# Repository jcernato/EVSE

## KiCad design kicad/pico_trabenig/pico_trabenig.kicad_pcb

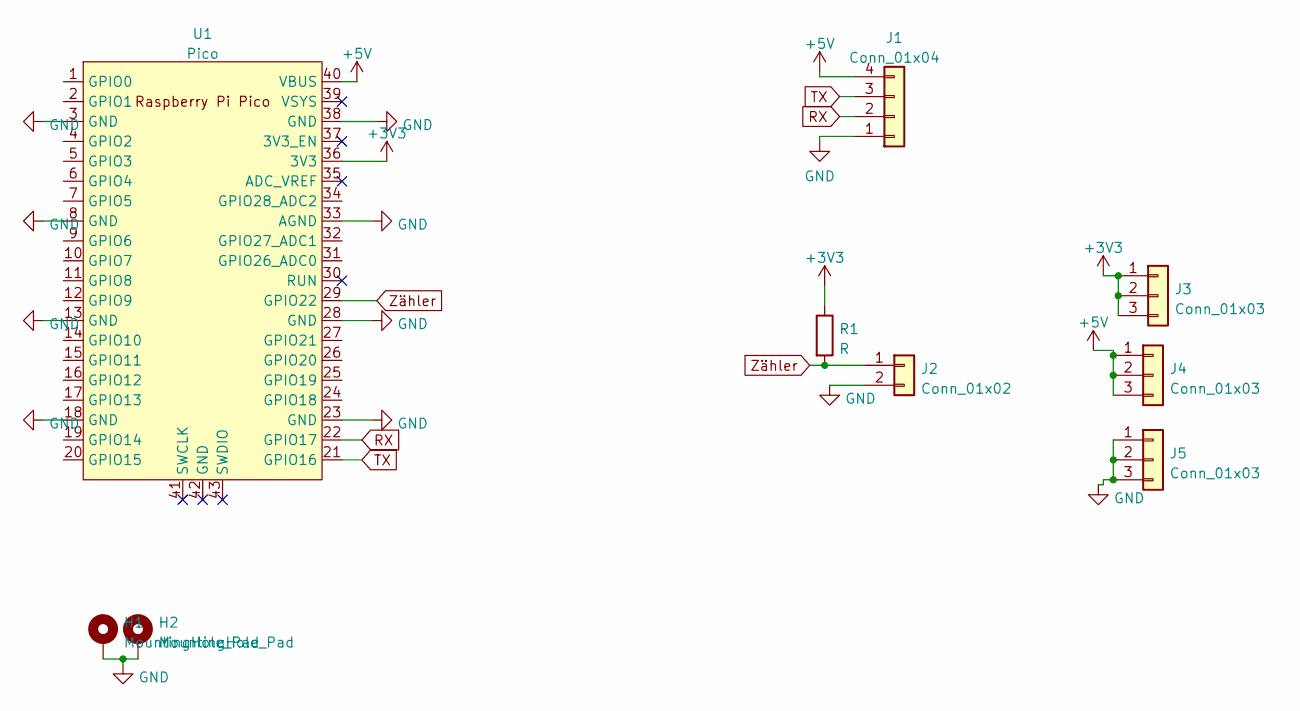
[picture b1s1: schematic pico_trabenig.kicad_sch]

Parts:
H1, H2: MountingHole_Pad; MountingHole_3.2mm_M3_DIN965_Pad
J1: Conn_01x04; JST_XH_B4B-XH-A_1x04_P2.50mm_Vertical
J2: Conn_01x02; JST_XH_B2B-XH-A_1x02_P2.50mm_Vertical
J3, J4, J5: Conn_01x03; PinSocket_1x03_P2.54mm_Vertical
R1: R; R_1206_3216Metric
U1: Pico; RPi_Pico_SMD_TH

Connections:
+3V3: J3.1, J3.2, J3.3, R1.1, U1.36 (3V3)
+5V: J1.4, J4.1, J4.2, J4.3, U1.40 (VBUS)
GND: H1.1, H2.1, J1.1, J2.2, J5.1, J5.2, J5.3, U1.3 (GND), U1.8 (GND), U1.13 (GND), U1.18 (GND), U1.23 (GND), U1.28 (GND), U1.33 (AGND), U1.38 (GND)
RX: J1.2, U1.22 (GPIO17)
TX: J1.3, U1.21 (GPIO16)
Zähler: J2.1, R1.2, U1.29 (GPIO22)

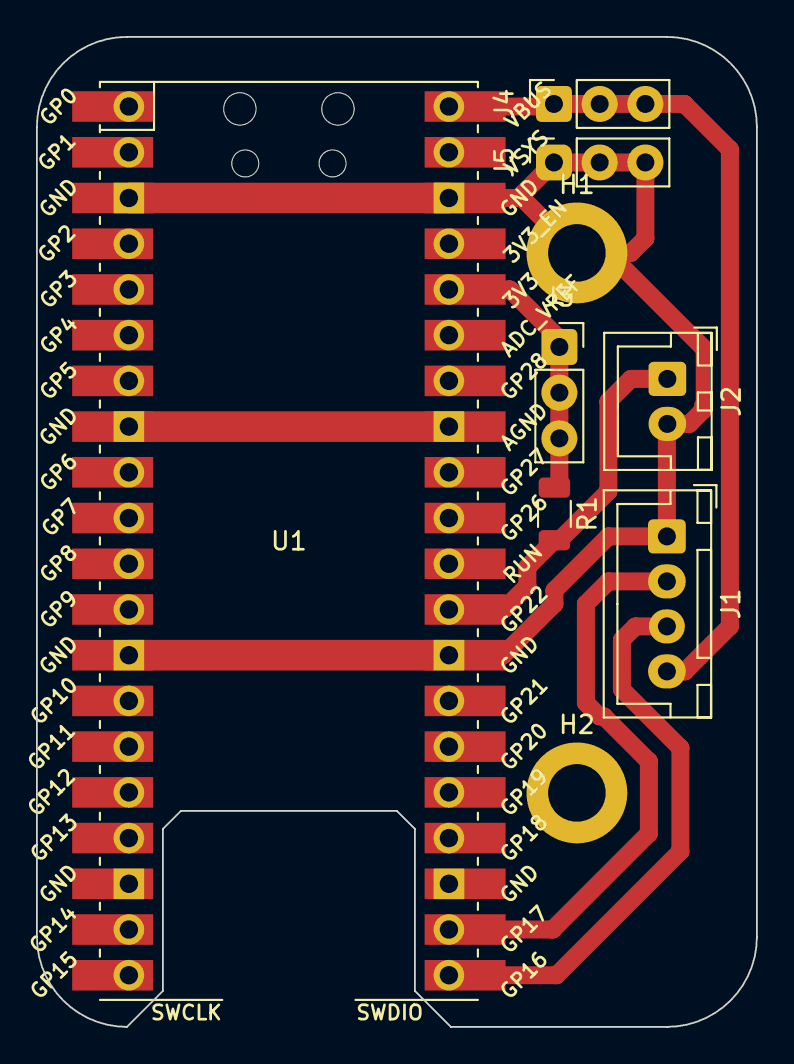
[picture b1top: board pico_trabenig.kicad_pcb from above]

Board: 2 copper layers, 40.0 x 55.0 mm, 9 parts (0 on the bottom side), 6 nets.

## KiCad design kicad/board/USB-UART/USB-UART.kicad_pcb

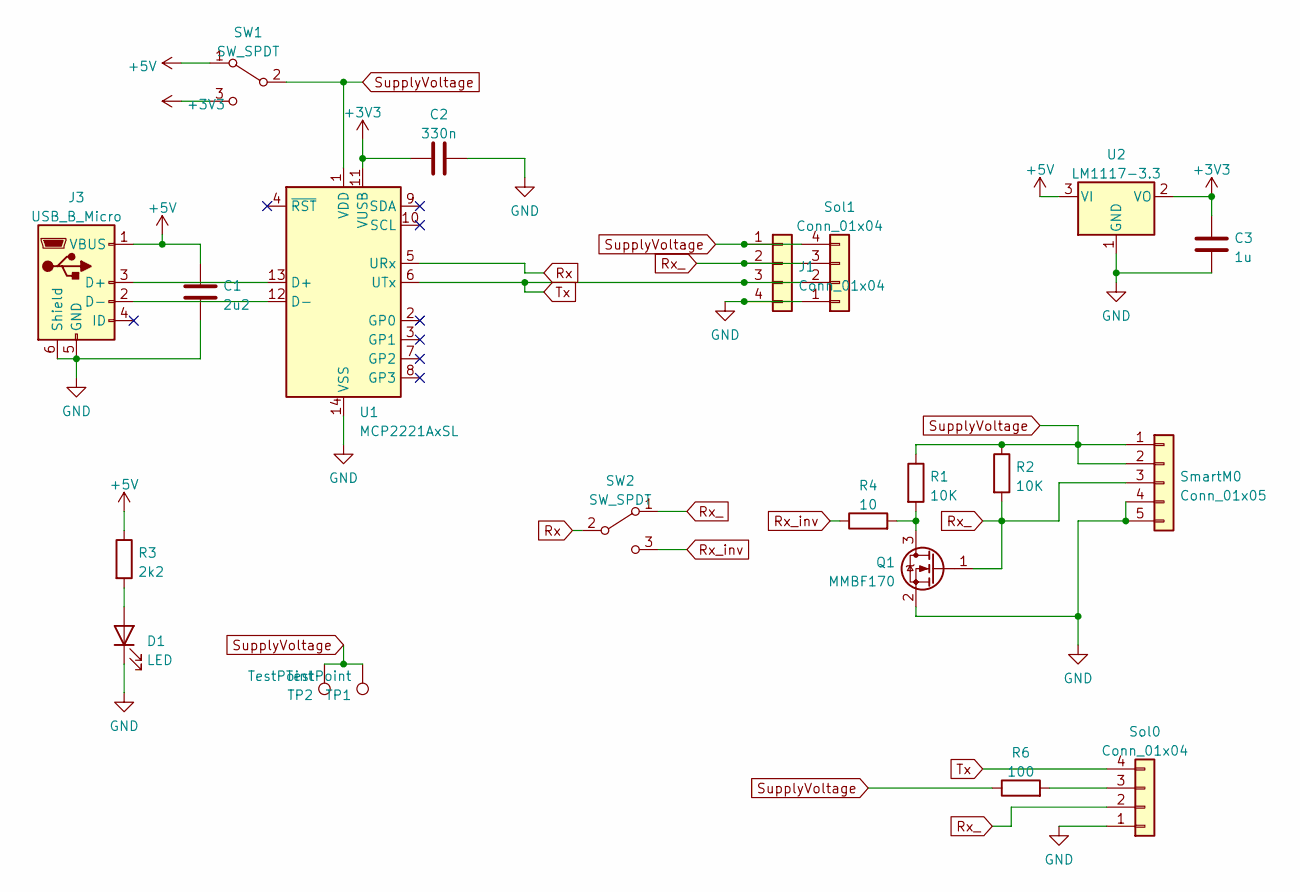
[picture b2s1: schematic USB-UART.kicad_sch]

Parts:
C1: 2u2; C_Radial_D5.0mm_H5.0mm_P2.00mm
C2: 330n; C_1206_3216Metric
C3: 1u; C_1206_3216Metric
D1: LED; LED_1206_3216Metric
J1: Conn_01x04; Molex_KK-254_AE-6410-04A_1x04_P2.54mm_Vertical
J3: USB_B_Micro; USB_Mini-B_Wuerth_65100516121_Horizontal
Q1: MMBF170; SOT-23
R1, R2: 10K; R_1206_3216Metric
R3: 2k2; R_1206_3216Metric
R4: 10; R_1206_3216Metric
R6: 100; R_1206_3216Metric
SW1, SW2: SW_SPDT; SW_Slide_1P2T_CK_OS102011MS2Q
SmartM0: Conn_01x05; JST_PH_B5B-PH-K_1x05_P2.00mm_Vertical
Sol0, Sol1: Conn_01x04; JST_PH_B4B-PH-K_1x04_P2.00mm_Vertical
TP1, TP2: TestPoint; Pin_D1.0mm_L10.0mm
U1: MCP2221AxSL; SOIC-14_3.9x8.7mm_P1.27mm
U2: LM1117-3.3; SOT-223-3_TabPin2

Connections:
+3V3: C2.1, C3.2, SW1.3 (C), U1.11 (VUSB), U2.2 (VO)
+5V: C1.2, J3.1 (VBUS), R3.1, SW1.1 (A), U2.3 (VI)
GND: C1.1, C2.2, C3.1, D1.1 (K), J1.4, J3.5 (GND), J3.6 (Shield), Q1.2 (S), SmartM0.4, SmartM0.5, Sol0.1, Sol1.1, U1.14 (VSS), U2.1 (GND)
unnamed: D1.2 (A), R3.2
unnamed: J3.2 (D-), U1.12 (D-)
unnamed: J3.3 (D+), U1.13 (D+)
unnamed: Q1.3 (D), R1.2, R4.2
unnamed: R6.2, Sol0.3
Rx: SW2.2 (B), U1.5 (URx)
Rx_: J1.2, Q1.1 (G), R2.2, SW2.1 (A), SmartM0.3, Sol0.2, Sol1.3
Rx_inv: R4.1, SW2.3 (C)
SupplyVoltage: J1.1, R1.1, R2.1, R6.1, SW1.2 (B), SmartM0.1, SmartM0.2, Sol1.4, TP1.1, TP2.1, U1.1 (VDD)
Tx: J1.3, Sol0.4, Sol1.2, U1.6 (UTx)

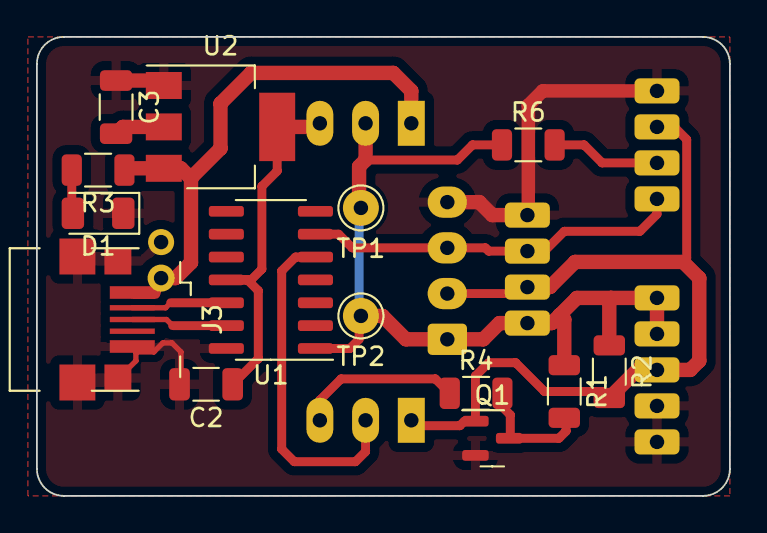
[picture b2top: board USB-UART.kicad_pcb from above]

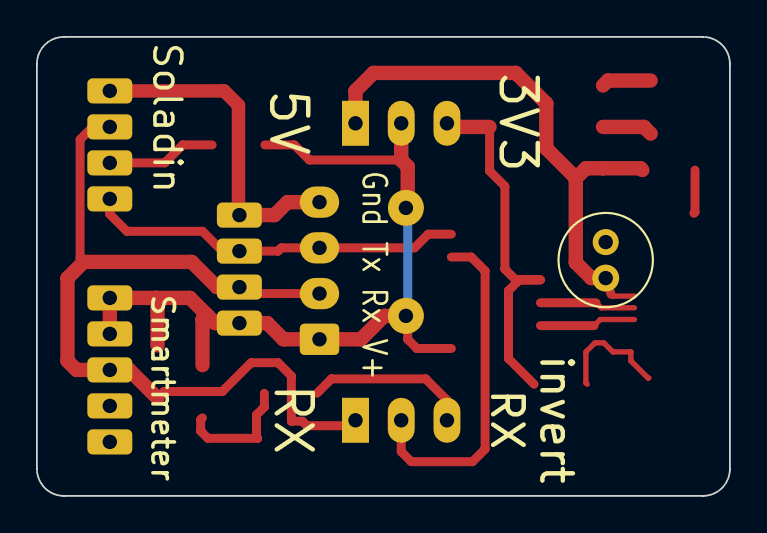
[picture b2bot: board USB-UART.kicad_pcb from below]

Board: 2 copper layers, 38.5 x 25.5 mm, 21 parts (7 on the bottom side), 13 nets.

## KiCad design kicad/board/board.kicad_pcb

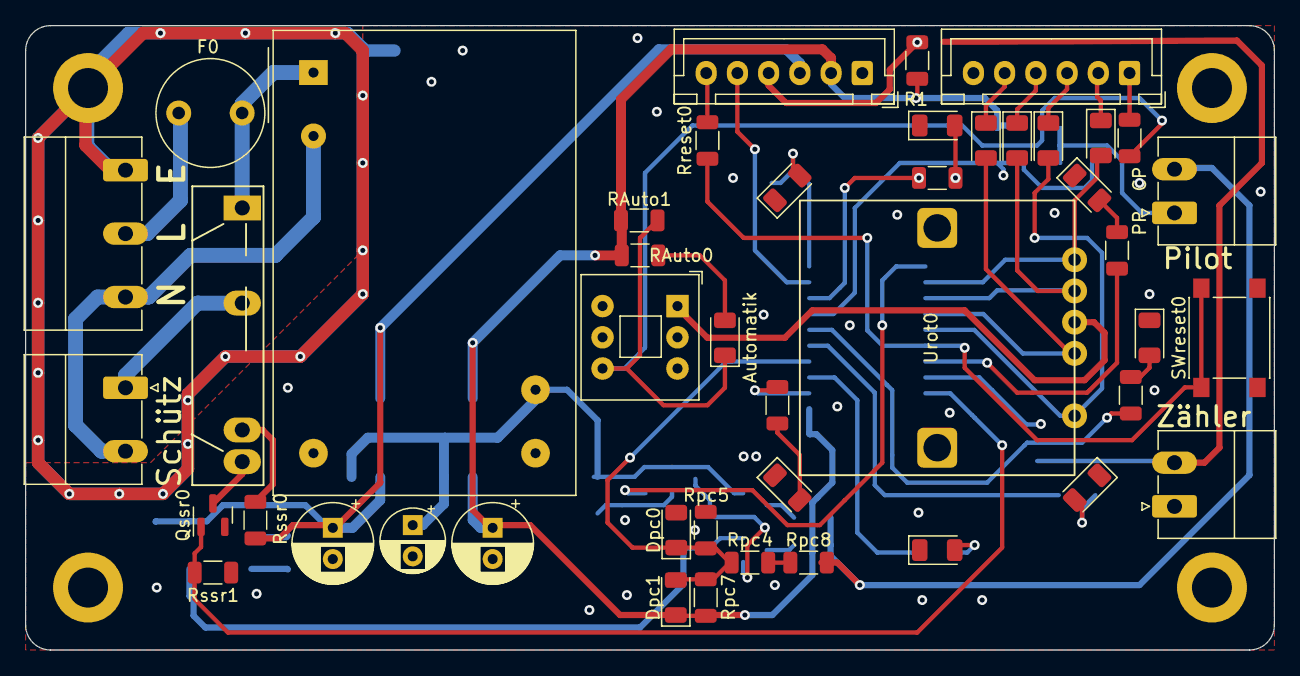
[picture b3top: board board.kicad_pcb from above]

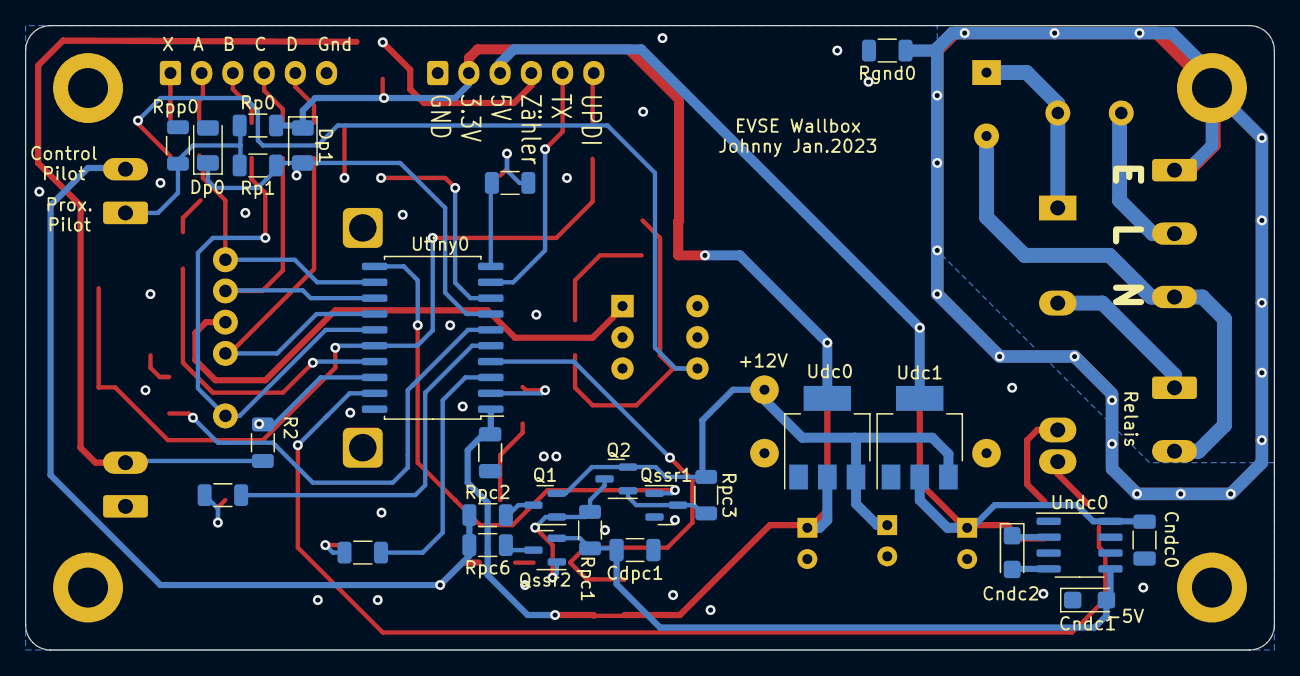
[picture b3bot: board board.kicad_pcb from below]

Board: 4 copper layers, 100.0 x 50.0 mm, 76 parts (27 on the bottom side), 53 nets.

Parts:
Cd0: 10p; C_1206_3216Metric
Cdc0: 22u; CP_Radial_D5.0mm_P2.50mm
Cdc1, Cdc2: 100u; CP_Radial_D6.3mm_P2.50mm
Cdpc1: 10p; C_1206_3216Metric
Cndc0: 10p; C_1206_3216Metric
Cndc1, Cndc2: 10u; CP_EIA-3216-18_Kemet-A
DLed0, DLed1, DLed2, DLed3, DLed4, DLed5, DLed6: LED; LED_1206_3216Metric
DLed_auto0: LED; LED_1206_3216Metric
Dc0, Dc1, Dc2, Dc3: D; D_1206_3216Metric
Dp0, Dp1: D; D_1206_3216Metric
Dpc0, Dpc1: D; D_1206_3216Metric
F0: 100m; Fuse_Littelfuse_372_D8.50mm
H0, H1, H2, H3: MountingHole_Pad; MountingHole_3.2mm_M3_DIN965_Pad
J0: Netz; PhoenixContact_MC_1,5_3-G-5.08_1x03_P5.08mm_Horizontal
J1: Conn_01x02; PhoenixContact_MC_1,5_2-G-3.5_1x02_P3.50mm_Horizontal
J2: Schütz; PhoenixContact_MC_1,5_2-G-5.08_1x02_P5.08mm_Horizontal
J3: Pilot; PhoenixContact_MC_1,5_2-G-3.5_1x02_P3.50mm_Horizontal
Jcontrol0, Jcontrol1: Conn_01x06; JST_XH_B6B-XH-A_1x06_P2.50mm_Vertical
PSACDC0: IRM-03-12; Converter_ACDC_MeanWell_IRM-03-xx_THT
Q1, Q2: IRLML5203; SOT-23
Qssr0, Qssr1, Qssr2: MMBF170; SOT-23
R1: 10K; R_1206_3216Metric
R2: 1K; R_1206_3216Metric
RAuto0: 1K; R_1206_3216Metric
RAuto1: 100K; R_1206_3216Metric
RAuto2: 10K; R_1206_3216Metric
RLed0, RLed1, RLed2, RLed3, RLed4, RLed5, RLed6: 470; R_1206_3216Metric
Rgnd0: 100; R_1206_3216Metric
Rp0: 3K3; R_1206_3216Metric
Rp1: 4K7; R_1206_3216Metric
Rpc1: 3k3; R_1206_3216Metric
Rpc2, Rpc6: 1K; R_1206_3216Metric
Rpc3: 10k; R_1206_3216Metric
Rpc4, Rpc7, Rpc8: 100K; R_1206_3216Metric
Rpc5: 68K; R_1206_3216Metric
Rpp0: 1K5; R_1206_3216Metric
Rreset0: 4K7; R_1206_3216Metric
Rssr0: 100; R_1206_3216Metric
Rssr1: 10K; R_1206_3216Metric
SWAuto0: SW_Push_DPDT; SW_Push_2P2T_Toggle_CK_PVA2xxH1xxxxxxV2
SWreset0: SW_Push; SW_Push_1P1T_NO_6x6mm_H9.5mm
Udc0: LM1117-3.3; SOT-223-3_TabPin2
Udc1: AZ1117-5.0; SOT-223-3_TabPin2
Undc0: LTC1044; SOIC-8_3.9x4.9mm_P1.27mm
Urot0: PAC18R
Ussr0: S202S01; SIP4_Sharp-SSR_P7.62mm_Straight
Utiny0: ATtiny1616-S; SOIC-20W_7.5x12.8mm_P1.27mm

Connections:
+3V3: Cd0.1, Cdc2.1, Dp1.1 (K), Dpc1.1 (K), Jcontrol1.2, R1.1, RAuto0.2, RAuto1.2, Rp0.2, Rpc7.2, Udc0.2 (VO), Utiny0.1 (VCC)
+5V: Cdc1.1, Cndc0.1, Jcontrol1.3, Rssr0.1, Udc1.2 (VO), Undc0.8 (V+)
+12V: Cdc0.1, PSACDC0.16 (+Vo), Q1.2 (S), Q2.2 (S), Rpc3.1, Udc0.3 (VI), Udc1.3 (VI)
-5V: Cdpc1.2, Cndc1.2, Qssr2.2 (S), Rpc1.2, Undc0.5 (VOUT)
/ACL: F0.1, J0.2
/ACS: J2.1, Ussr0.2
A: Dc3.2 (A), Urot0.1, Utiny0.12 (PC0)
AC: F0.2, PSACDC0.1 (AC/L), Ussr0.1
B: Dc2.2 (A), Urot0.2, Utiny0.15 (PC3)
C: Dc1.2 (A), Urot0.3, Utiny0.13 (PC1)
CP-Read: Dpc0.1 (K), Dpc1.2 (A), Rpc4.1, Rpc5.2, Rpc7.1, Utiny0.4 (PA6)
Control Pilot: J3.2, Rpc2.1, Rpc6.2, Rpc8.2
D: Dc0.2 (A), Urot0.4, Utiny0.14 (PC2)
Earth: H0.1, J0.1, Rgnd0.1
GND: Cd0.2, Cdc0.2, Cdc1.2, Cdc2.2, Cdpc1.1, Cndc0.2, Cndc1.1, DLed0.1 (K), DLed1.1 (K), DLed2.1 (K), DLed3.1 (K), DLed4.1 (K), DLed5.1 (K), DLed6.1 (K), Dp0.2 (A), Dpc0.2 (A), H1.1, H2.1, H3.1, J1.1, Jcontrol0.6, Jcontrol1.1, PSACDC0.14 (-Vo), Qssr0.2 (S), Qssr1.2 (S), Rgnd0.2, Rpc5.1, Rpp0.1, Rssr1.1, SWAuto0.1 (A), SWAuto0.3 (C), SWAuto0.5 (B), SWreset0.2, Udc0.1 (GND), Udc1.1 (GND), Undc0.3 (GND), Urot0.5 (gnd), Utiny0.20 (GND)
Led0: RLed0.1, Utiny0.10 (PB1)
Led1: R2.2, Utiny0.18 (PA2)
Led2: RLed2.1, Utiny0.17 (PA1)
Led3: RLed3.1, Utiny0.6 (PB5)
Led4: RLed4.1, Utiny0.5 (PA7)
Led5: RLed5.1, Utiny0.3 (PA5)
Led6: RLed6.1, Utiny0.2 (PA4)
unnamed: Cndc2.1, Undc0.2 (CAP+)
unnamed: Cndc2.2, Undc0.4 (CAP-)
unnamed: DLed0.2 (A), RLed0.2
unnamed: DLed1.2 (A), J1.2, R2.1, RLed1.2
unnamed: DLed2.2 (A), RLed2.2
unnamed: DLed3.2 (A), RLed3.2
unnamed: DLed4.2 (A), RLed4.2
unnamed: DLed5.2 (A), RLed5.2
unnamed: DLed6.2 (A), RLed6.2
unnamed: DLed_auto0.2 (A), RAuto0.1
unnamed: Dc0.1 (K), Jcontrol0.5
unnamed: Dc1.1 (K), Jcontrol0.4
unnamed: Dc2.1 (K), Jcontrol0.3
unnamed: Dc3.1 (K), Jcontrol0.2
unnamed: Jcontrol0.1, RAuto2.1
unnamed: Q1.1 (G), Q2.3 (D), Qssr2.1 (G), Rpc1.1
unnamed: Q1.3 (D), Rpc2.2
unnamed: Q2.1 (G), Qssr1.3 (D), Rpc3.2
unnamed: Qssr0.3 (D), Ussr0.4
unnamed: Qssr2.3 (D), Rpc6.1
unnamed: Rpc4.2, Rpc8.1
unnamed: Rreset0.1, SWreset0.1, Utiny0.16 (~RESET/PA0)
unnamed: Rssr0.2, Ussr0.3
PP Read: DLed_auto0.1 (K), Dp0.1 (K), Dp1.2 (A), RAuto1.1, RAuto2.2, SWAuto0.6 (C), Utiny0.7 (PB4)
PWM: Qssr1.1 (G), Utiny0.11 (PB0)
Proximity Pilot: J3.1, Rp0.1, Rp1.1, Rpp0.2
Relais: Qssr0.1 (G), Rssr1.2, Utiny0.19 (PA3)
UPDI: Jcontrol1.6, Rreset0.2
Uart_RX: Jcontrol1.4, R1.2, RLed1.1, Utiny0.8 (PB3)
Uart_TX: Jcontrol1.5, Utiny0.9 (PB2)
VAC: J0.3, J2.2, PSACDC0.3 (AC/N)

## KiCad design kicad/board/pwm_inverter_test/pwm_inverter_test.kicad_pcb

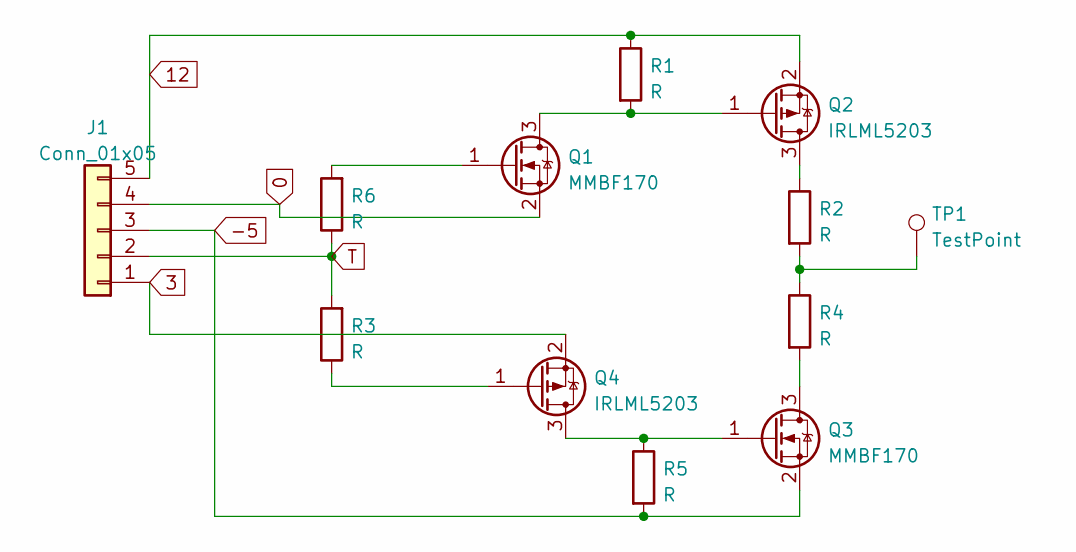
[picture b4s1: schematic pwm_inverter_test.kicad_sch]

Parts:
J1: Conn_01x05; JST_PH_B5B-PH-K_1x05_P2.00mm_Vertical
Q1, Q3: MMBF170; SOT-23
Q2, Q4: IRLML5203; SOT-23
R1, R2, R3, R4, R5, R6: R; R_1206_3216Metric
TP1: TestPoint; Pin_D0.7mm_L6.5mm_W1.8mm_FlatFork

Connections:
0: J1.4, Q1.2 (S)
3: J1.1, Q4.2 (S)
12: J1.5, Q2.2 (S), R1.1
-5: J1.3, Q3.2 (S), R5.2
unnamed: Q1.3 (D), Q2.1 (G), R1.2
unnamed: Q3.1 (G), Q4.3 (D), R5.1
unnamed: Q4.1 (G), R3.1
unnamed: Q2.3 (D), R2.1
unnamed: R2.2, R4.1, TP1.1
unnamed: Q3.3 (D), R4.2
unnamed: Q1.1 (G), R6.2
T: J1.2, R3.2, R6.1

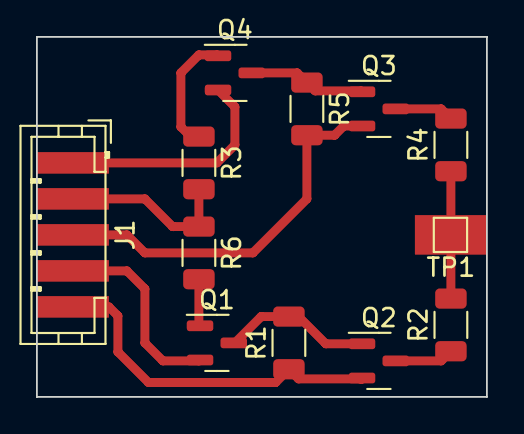
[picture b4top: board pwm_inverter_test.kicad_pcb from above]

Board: 2 copper layers, 25.0 x 20.0 mm, 12 parts (0 on the bottom side), 12 nets.

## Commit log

2022-05-16 init
2023-01-16 schematic für ersten prototypen fertig
2023-01-18 Hardware: PCB wie gefräst
    Auf Fräsen optimiert. d.h.:
    -> Vias auf 1.6x1.0 mm vergrößert
    -> An allen Pins die auf Vorderseite angebunden sind Löcher
    vergrößert (für Buchsen)
    Probleme:
    -> Falscher Footprint Solid state relais
2023-01-20 firmware: pinconfig und pwm config soweit fertig
2023-01-20 3d-teile: Provisorischen Drehknopf gedruckt
2023-01-22 save
2023-01-24 firmware: objektorientierte state machine konzeptioniert
2023-01-25 hardware: kicad board bestellt
    simplifiziert:
    Strom sowie Fehlerstrom werden durch Hauptsicherung und FI gesichert.
    AC-Check is a recht sinnlos weil gegen ein hängendes Relais kannst
    eh nit viel tun.
    Diodencheck macht sinn, wird auch mit -5V statt den Spezifizierten -12V
    duchgeführt, sollt genauso funktionieren, meine LTC1044 halten max 9V aus.
2023-02-01 kicad: USB-UART für Mauki
2023-02-11 firmware: pins an neues pcb angepasst
2023-02-15 firmware: save, 3d-parts: beleuchteter Text2
2023-02-15 hardware: korrekturen fehlerhaftes pcb
2023-02-15 firmware: Umstellung auf remote via UART
2023-02-19 firmware: serial protokoll neu (mit checksum)
    magic number (0xb4)
    timeout für serial 5 min
    opt. force auto (0xb5)
2023-02-24 firmware: Erlaube beliebige Ladeleistung
    Zuvor wurde set_pwm nur mit vordefinierten Ladeleistungen entprechend
    der Encoder-Stellung aufgerufen.
    Im automatik modus kann aber ein arbiträrer Wert zwischen 1000 und 3600
    Watt angegeben werden.
2023-02-25 firmware: großer bugfix
    -> pinconfig - ladeleistung auf 3.4 KW begrenzt
    -> custom classes:
    - erlaube serial input = 0 ohne Fehlermeldung
    - float_buf vergrößert (Angst vor BufferOF)
    - führe automatik als globale Variable
    -> functions:
2023-02-26 firmware: Umstrukturierung + serielles Protokoll
    Umstrukturiert in header + cpp file
    serielles Protokoll:
    5 Befehle sind definiert:
    L ... setze Ladeleistung
    F ... force automatik modus + setze Ladeleistung
    R ... reset
2023-02-26 firmware: bugfix + kosmetik + watchdog
    bug: mit automatik in detected war kein rückstufen in standby möglich
2023-03-10 firmware: einige bugfixes + feature (force auto)
    force-auto: force modus bleibt bestehen, kann entweder durch
    'L' command oder durch manuelles drücken des auto-knopfes
    zurückgesetzt werden.
2023-03-15 firmware: coding style angepasst
2023-03-15 firmware: refactoring
2023-07-01 save + restore .gitignore
2023-07-03 firmware: code aufteilung in mehrere files
    -> serielle Kommunikation in serial.h/cpp ausgelagert
    -> state class declaration und individuelle set/run funtions in
    states.h/cpp ausgelagert
    code compiliert, nicht getestet!
2023-08-12 firmware: wallbox großes refactoring
    funktionen zerteilt, neue einfache helper hinzugefügt -> code
    leserlicher gemacht
    serielle kommunkation funktioniert, teil reagiert aber auf nix (set
    ladeleistung, encoder, automatik-knopf
2023-08-13 lots of debugging
2023-08-13 firmware: pico -> umstellung auf mqtt get/set/force
    läuft, aber noch nicht stabil (reagiert nach einiger Zeit nicht mehr)
2023-08-14 firmware: wallbox - umbau update logik
    encoder-led blinkt im auto-modus
    wenn mqtt daten älter als 5 min (out of date) - fallback in
    manuellen modus (ladeleistung gemäß encoder)
    dadurch soll verhindert werden dass nicht geladen wird wenn die
    verbindung zum server ausfällt
2023-08-14 firmware: pico - aufräumen
    viel aufgeräumt und umstrukturiert
    einige verbesserungen bez. zuverlässigkeit:
    -> watchdog integriert
    -> read_serial verbessert (wartet auf fetigen transfer)
    TODO:
    -> mehr resilienz - verbindungsfehler erkennen (mqtt, wlan) und
2023-08-15 firmware: pico + wallbox -> error_code
    error_code eingeführt und als 14. byte in serial-status msg
    integriert.
    error codes:
    0: no error
    1: manual error injected
    2: diode check failed
2023-08-17 firmware: pico - verbindung und wallbox
    wallbox.py beinhaltet wallbox klasse
    verbindung is softlink zu githubs/soladin/software
2023-11-12 Integration Counter S0 (Stromzähler) Trabenig
    schnelles anpassen in Maukis Garage
2024-01-21 MQTT Topics umbenannt
2024-12-28 Umbenennung von header-files von .h auf .hpp
    VSCode zickt sonst beim syntax-highlighting ...
